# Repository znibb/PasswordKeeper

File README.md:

# PasswordKeeper
Ever gotten tired manually inputing your password everytime you unlock your desktop? PasswordKeeper let's you use a RFID/NFC tag to input a password into your computer!
## About

The device consists of a custom designed circuit that uses an Atmega32u4 MCU to interface a MFRC522 contactless reader to any computer by emulating a keyboard over a USB connection, no driver or external software required!

The device stores a list of tags with an assoiciated password in the EEPROM of the MCU. When a user scans a tag the program returns the corresponding password as emulated keyboard presses. The sketch used to store user credentials in EEPROM can be found here: https://github.com/znibb/PasswordKeeper_loadData/.

## Usage
### Store user credentials
1. Download the loadData sketch from: https://github.com/znibb/PasswordKeeper_loadData/.
2. Copy `src/PasswordKeeper_loadData.ino.template` to `src/PasswordKeeper_loadData.ino`.
3. Edit loadData sketch with appropriate user credentials.
4. Upload loadData sketch.
5. Open a serial connection to the device to initialize the writing to EEPROM and to get feedback on the results.
6. Done.

### Prepare for operation
1. Clone/download the sketch from this repository.
2. Upload sketch.
3. Ready for use!

## Tips & tricks
- Don't know the UID of your tag? 
  - Upload the sketch and start a serial monitor. The sketch will output the UID of any scanned tag on the serial bus.

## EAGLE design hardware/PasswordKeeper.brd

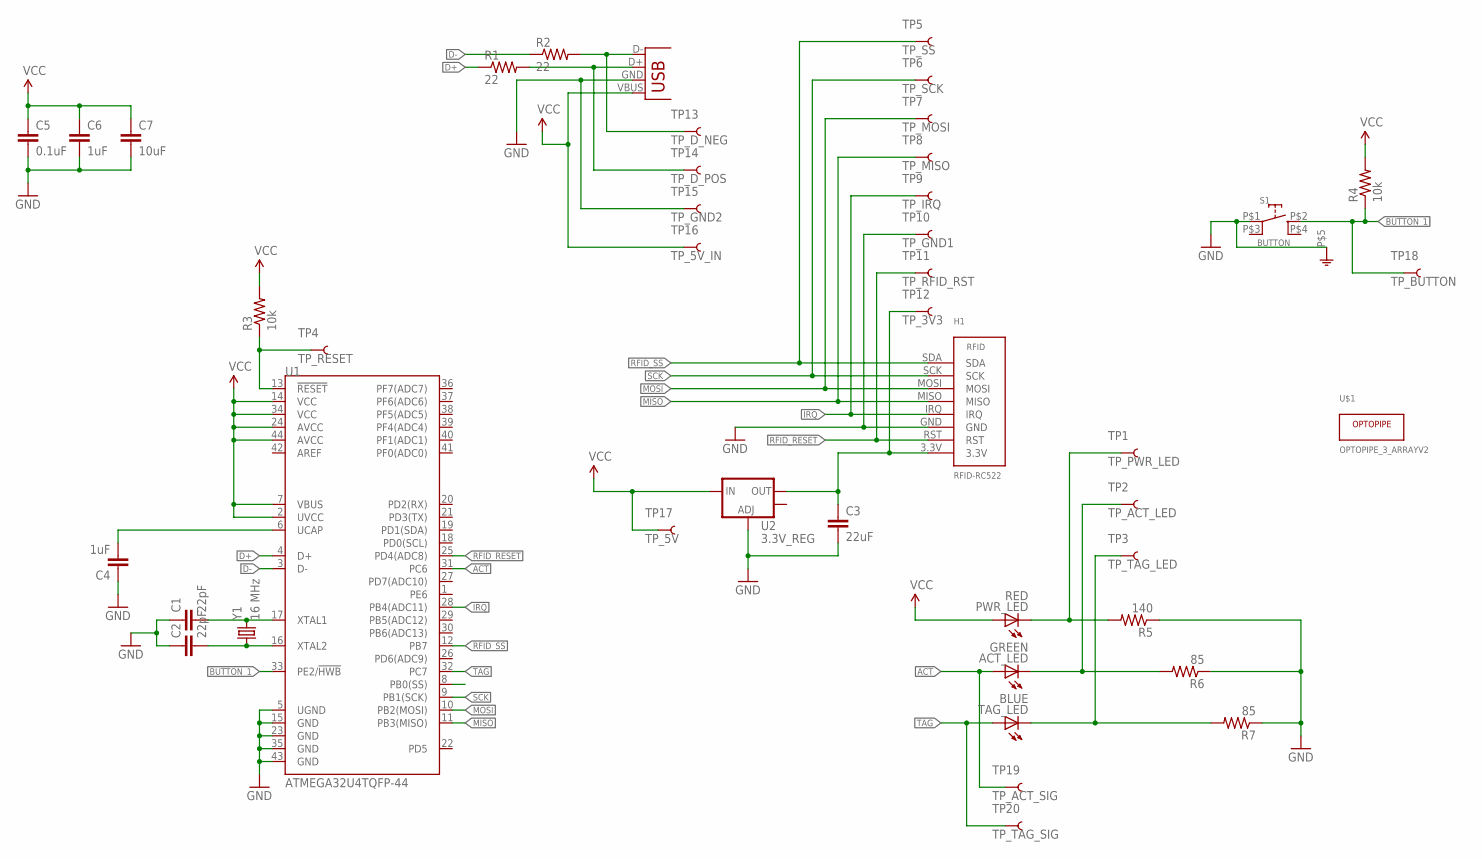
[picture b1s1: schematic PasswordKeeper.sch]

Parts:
ACT_LED: GREEN; LED-1206
C1, C2: 22pF; 1206
C3: 22uF; 0805
C4, C6: 1uF; 1206
C5: 0.1uF; 1206
C7: 10uF; 1206
H1: RFID-RC522; EXT_RFID_READER
JP1: USB-A-H
PWR_LED: RED; LED-1206
R1, R2: 22; 1206
R3, R4: 10k; 1206
R5: 140; 1206
R6, R7: 85; 1206
S1: BUTTON; TACTILE_SWITCH_SMD_RIGHT_ANGLE
TAG_LED: BLUE; LED-1206
TP1: TP_PWR_LED; TP_15TH
TP2: TP_ACT_LED; TP_15TH
TP3: TP_TAG_LED; TP_15TH
TP4: TP_RESET; TP_15TH
TP5: TP_SS; TP_15TH
TP6: TP_SCK; TP_15TH
TP7: TP_MOSI; TP_15TH
TP8: TP_MISO; TP_15TH
TP9: TP_IRQ; TP_15TH
TP10: TP_GND1; TP_15TH
TP11: TP_RFID_RST; TP_15TH
TP12: TP_3V3; TP_15TH
TP13: TP_D_NEG; TP_15TH
TP14: TP_D_POS; TP_15TH
TP15: TP_GND2; TP_15TH
TP16: TP_5V_IN; TP_15TH
TP17: TP_5V; TP_15TH
TP18: TP_BUTTON; TP_15TH
TP19: TP_ACT_SIG; TP_15TH
TP20: TP_TAG_SIG; TP_15TH
U1: ATMEGA32U4TQFP-44; TQFP44
U2: 3.3V_REG; SOT223
U$1: OPTOPIPE_3_ARRAYV2; 515-1000_V2
Y1: 16 MHz; HC49UP

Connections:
3.3V: C3.1, H1.3.3V, TP12.P$1, U2.2 (OUT)
ACT: ACT_LED.A, TP19.P$1, U1.31 (PC6)
BUTTON_1: R4.1, S1.P$2, TP18.P$1, U1.33 (PE2/!HWB)
D+: R1.1, U1.4 (D+)
D-: R2.1, U1.3 (D-)
GND: C1.1, C2.1, C3.2, C4.1, C5.2, C6.2, C7.2, H1.GND, JP1.GND (VBUS), R5.1, R6.1, R7.1, S1.P$1, S1.P$5, TP10.P$1, TP15.P$1, U1.5 (UGND), U1.15 (GND), U1.23 (GND), U1.35 (GND), U1.43 (GND), U2.1 (ADJ)
IRQ: H1.IRQ, TP9.P$1, U1.28 (PB4(ADC11))
MISO: H1.MISO, TP8.P$1, U1.11 (PB3(MISO))
MOSI: H1.MOSI, TP7.P$1, U1.10 (PB2(MOSI))
unnamed: JP1.D- (D+), R2.2, TP13.P$1
unnamed: JP1.D+ (D-), R1.2, TP14.P$1
unnamed: C1.2, U1.17 (XTAL1), Y1.2
unnamed: C2.2, U1.16 (XTAL2), Y1.1
unnamed: C4.2, U1.6 (UCAP)
unnamed: PWR_LED.C, R5.2, TP1.P$1
unnamed: ACT_LED.C, R6.2, TP2.P$1
unnamed: R7.2, TAG_LED.C, TP3.P$1
PROG_SS: U1.8 (PB0(SS))
RESET: R3.1, TP4.P$1, U1.13 (!RESET)
RFID_RESET: H1.RST, TP11.P$1, U1.25 (PD4(ADC8))
RFID_SS: H1.SDA, TP5.P$1, U1.12 (PB7)
SCK: H1.SCK, TP6.P$1, U1.9 (PB1(SCK))
TAG: TAG_LED.A, TP20.P$1, U1.32 (PC7)
VCC: C5.1, C6.1, C7.1, JP1.VBUS (GND), PWR_LED.A, R3.2, R4.2, TP16.P$1, TP17.P$1, U1.2 (UVCC), U1.7 (VBUS), U1.14 (VCC), U1.24 (AVCC), U1.34 (VCC), U1.44 (AVCC), U2.3 (IN)

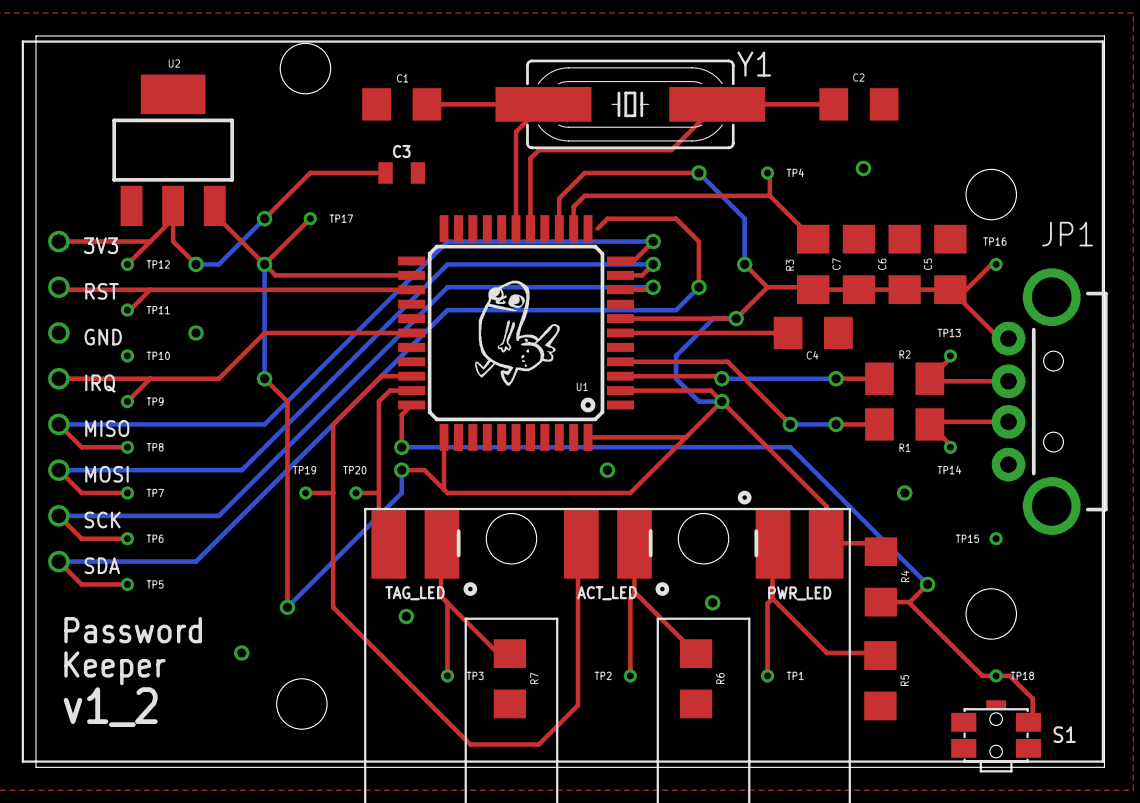
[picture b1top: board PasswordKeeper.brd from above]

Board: 2 copper layers, 59.4 x 40.6 mm, 44 parts (0 on the bottom side), 23 nets.

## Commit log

2016-11-26 Added fuse printout files to .gitignore
2016-11-27 Obfuscated master tag ID
2016-12-01 Script to burn bootloader using avrisp2 programmer
2016-12-01 Removed debug code and enabled keyboard output as default
2016-12-01 Updated fuse values
2016-12-01 Minor fix
2016-12-01 Travis confing file
2016-12-10 Increased antenna gain and fixed error in reading button state
2016-12-10 Added platformio-specific folders
2016-12-28 Implemented support for multiple tags with one associated password each
2017-01-02 Changed credential storage from source code to EEPROM
2017-01-02 Moved 'magic numbers' to named parameters
2017-04-27 Cleaned up bootloader tools and added relevant readme
2017-05-31 Added PCB files
2017-06-02 Revert "Added PCB files"
    This reverts commit 08d9288e047e3d3013372883bf24a64ee6211b8b.
2017-06-02 Revert "Initial commit". Messed up commit messages.
    This reverts commit a167ed2f3c9f163b5252ba3184aee50a860bac41.
2017-06-02 Clean up
2017-06-02 Added TagData library to support v2 functionality
2017-06-02 Changed program to read array sizes from EEPROM instead of having to transfer them manually from PasswordKeeper_loadData
2017-07-29 Added "watermarking" source file
2017-07-29 Added gerber zip for version 1.2
2017-07-29 HW version 1.2

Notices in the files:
parts and their libraries:
SparkFun-PowerIC: Licensing: Creative Commons ShareAlike 4.0 International - https://creativecommons.org/licenses/by-sa/4.0
